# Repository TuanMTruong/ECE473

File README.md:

#Wireless room LED controller
ECE 473 project.

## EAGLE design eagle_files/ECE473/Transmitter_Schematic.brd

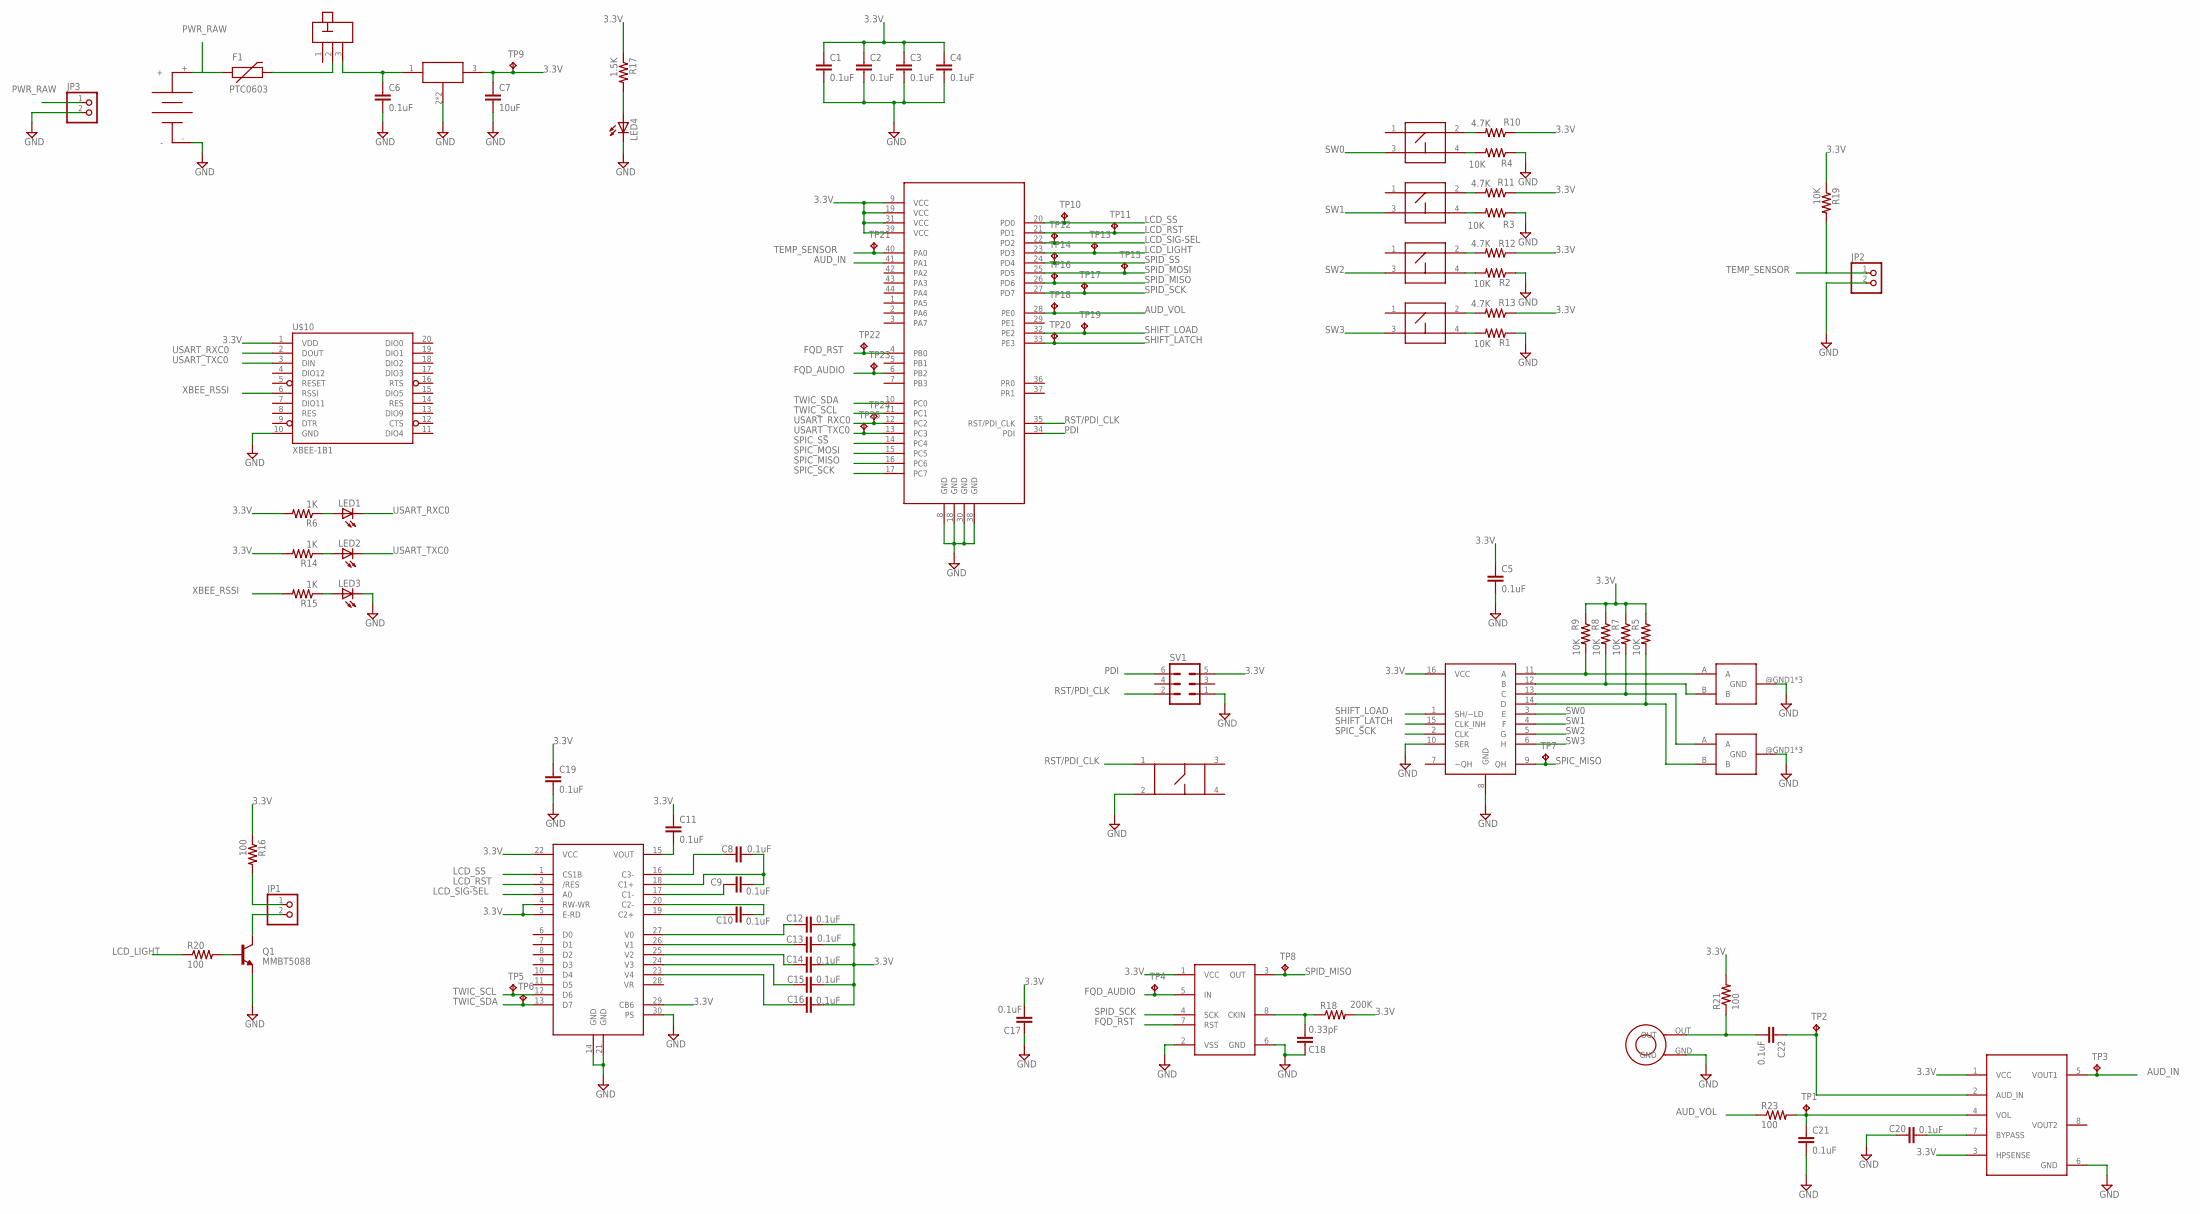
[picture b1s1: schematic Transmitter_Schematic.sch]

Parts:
C1, C2, C3, C4, C5, C6, C8, C9, C10, C11, C12, C13, C14, C15, C16, C17, C19, C20, C21, C22: 0.1uF; 0603-CAP
C7: 10uF; 0603-CAP
C18: 0.33pF; 0603-CAP
F1: PTC0603; 0603
JP1, JP2, JP3: PINHD-1X2; 1X02
LED1, LED2, LED3, LED4: LED0603; LED-0603
Q1: MMBT5088; SOT23
R1, R2, R3, R4, R5, R7, R8, R9, R19: 10K; 0603-RES
R6, R14, R15: 1K; 0603-RES
R10, R11, R12, R13: 4.7K; 0603-RES
R16, R20, R21, R23: 100; 0603-RES
R17: 1.5K; 0603-RES
R18: 200K; 0603-RES
SV1: MA03-2
SW0, SW1, SW2, SW3: SPARKFUN_TAC_BUTTONS
TP1, TP2, TP3, TP4, TP5, TP6, TP7, TP8, TP9, TP10, TP11, TP12, TP13, TP14, TP15, TP16, TP17, TP18, TP19, TP20, TP21, TP22, TP23, TP24, TP25: TPPAD1-13; P1-13
U$1: ATXMEGA32A4UTQFP44; QFP80P1200X1200X120-44N
U$6: 8B_SHIFT_REG; TSSOP16
U$7: MICRO_TAC_BUTTONS
U$8, U$9: ENCODER; EVE_GE1F2012B
U$10: XBEE-1B1; XBEE-1
U$11: LCD_CONNECTOR
U$12: 3.3V_REG_LDO; SOT223
U$13: 3XAA_BATT_HOLDER
U$14: SWITCH_SLIDE
U$15: FREQUENCY_DIVIDER; DIP08
U$16: LM4875; SOIC8
U$17: MICROPHONE; CMA-4544PF

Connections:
3.3V: C1.1, C2.1, C3.1, C4.1, C5.1, C7.1, C11.1, C12.2, C13.2, C14.2, C15.2, C16.2, C17.2, C19.1, R5.1, R6.2, R7.1, R8.1, R9.1, R10.1, R11.1, R12.1, R13.1, R14.2, R16.1, R17.1, R18.2, R19.1, R21.2, SV1.5, TP9.TP, U$1.9 (VCC), U$1.19 (VCC), U$1.31 (VCC), U$1.39 (VCC), U$6.16 (VCC), U$10.1 (VDD), U$11.4 (RW-WR), U$11.5 (E-RD), U$11.22 (VCC), U$11.29 (CB6), U$12.3, U$15.1 (VCC), U$16.1 (VCC), U$16.3 (HPSENSE)
AUD_IN: TP3.TP, U$1.41 (PA1), U$16.5 (VOUT1)
AUD_VOL: R23.1, TP18.TP, U$1.28 (PE0)
FQD_AUDIO: TP4.TP, TP23.TP, U$1.6 (PB2), U$15.5 (IN)
FQD_RST: TP22.TP, U$1.4 (PB0), U$15.7 (RST)
GND: C1.2, C2.2, C3.2, C4.2, C5.2, C6.2, C7.2, C17.1, C18.1, C19.2, C20.1, C21.2, JP2.2, JP3.2, LED3.C, LED4.C, Q1.2 (E), R1.1, R2.1, R3.1, R4.1, SV1.1, U$1.8 (GND), U$1.18 (GND), U$1.30 (GND), U$1.38 (GND), U$6.8 (GND), U$6.10 (SER), U$7.2, U$8.@GND1 (GND), U$8.@GND2 (GND), U$8.GND, U$9.@GND1 (GND), U$9.@GND2 (GND), U$9.GND, U$10.10 (GND), U$11.14 (GND), U$11.21 (GND), U$11.30 (PS), U$12.2, U$12.4, U$13.-, U$15.2 (VSS), U$15.6 (GND), U$16.6 (GND), U$17.GND
LCD_LIGHT: R20.1, TP13.TP, U$1.23 (PD3)
LCD_RST: TP11.TP, U$1.21 (PD1), U$11.2 (/RES)
LCD_SIG-SEL: TP12.TP, U$1.22 (PD2), U$11.3 (A0)
LCD_SS: TP10.TP, U$1.20 (PD0), U$11.1 (CS1B)
MIC_IN: C22.1, TP2.TP, U$16.2 (AUD_IN)
unnamed: R2.2, SW2.4
unnamed: C6.1, U$12.1, U$14.3
unnamed: C8.1, U$11.16 (C3-)
unnamed: C8.2, C9.2, U$11.18 (C1+)
unnamed: R3.2, SW1.4
unnamed: R4.2, SW0.4
unnamed: R1.2, SW3.4
unnamed: R5.2, U$6.14 (D), U$9.B
unnamed: C9.1, U$11.17 (C1-)
unnamed: R9.2, U$6.11 (A), U$8.A
unnamed: R8.2, U$6.12 (B), U$8.B
unnamed: R7.2, U$6.13 (C), U$9.A
unnamed: C10.2, U$11.20 (C2-)
unnamed: R10.2, SW0.2
unnamed: R11.2, SW1.2
unnamed: R12.2, SW2.2
unnamed: R13.2, SW3.2
unnamed: C10.1, U$11.19 (C2+)
unnamed: C12.1, U$11.27 (V0)
unnamed: C13.1, U$11.26 (V1)
unnamed: C14.1, U$11.25 (V2)
unnamed: C15.1, U$11.24 (V3)
unnamed: C16.1, U$11.23 (V4)
unnamed: JP1.1, R16.2
unnamed: C11.2, U$11.15 (VOUT)
unnamed: JP1.2, Q1.3 (C)
unnamed: F1.2, U$14.2
unnamed: LED1.A, R6.1
unnamed: LED2.A, R14.1
unnamed: LED3.A, R15.1
unnamed: LED4.A, R17.2
unnamed: Q1.1 (B), R20.2
unnamed: C22.2, R21.1, U$17.OUT
unnamed: C21.1, R23.2, TP1.TP, U$16.4 (VOL)
unnamed: C20.2, U$16.7 (BYPASS)
unnamed: C18.2, R18.1, U$15.8 (CKIN)
PDI: SV1.6, U$1.34 (PDI)
PWR_RAW: F1.1, JP3.1, U$13.+
RST/PDI_CLK: SV1.2, U$1.35 (RST/PDI_CLK), U$7.1
SHIFT_LATCH: TP20.TP, U$1.33 (PE3), U$6.15 (CLK_INH)
SHIFT_LOAD: TP19.TP, U$1.32 (PE2), U$6.1 (SH/~LD)
SPIC_MISO: TP7.TP, U$1.16 (PC6), U$6.9 (QH)
SPIC_MOSI: U$1.15 (PC5)
SPIC_SCK: U$1.17 (PC7), U$6.2 (CLK)
SPIC_SS: U$1.14 (PC4)
SPID_MISO: TP8.TP, TP16.TP, U$1.26 (PD6), U$15.3 (OUT)
SPID_MOSI: TP15.TP, U$1.25 (PD5)
SPID_SCK: TP17.TP, U$1.27 (PD7), U$15.4 (SCK)
SPID_SS: TP14.TP, U$1.24 (PD4)
SW0: SW0.3, U$6.3 (E)
SW1: SW1.3, U$6.4 (F)
SW2: SW2.3, U$6.5 (G)
SW3: SW3.3, U$6.6 (H)
TEMP_SENSOR: JP2.1, R19.2, TP21.TP, U$1.40 (PA0)
TWIC_SCL: TP5.TP, U$1.11 (PC1), U$11.12 (D6)
TWIC_SDA: TP6.TP, U$1.10 (PC0), U$11.13 (D7)
USART_RXC0: LED1.C, TP24.TP, U$1.12 (PC2), U$10.2 (DOUT)
USART_TXC0: LED2.C, TP25.TP, U$1.13 (PC3), U$10.3 (DIN)
XBEE_RSSI: R15.2, U$10.6 (RSSI)

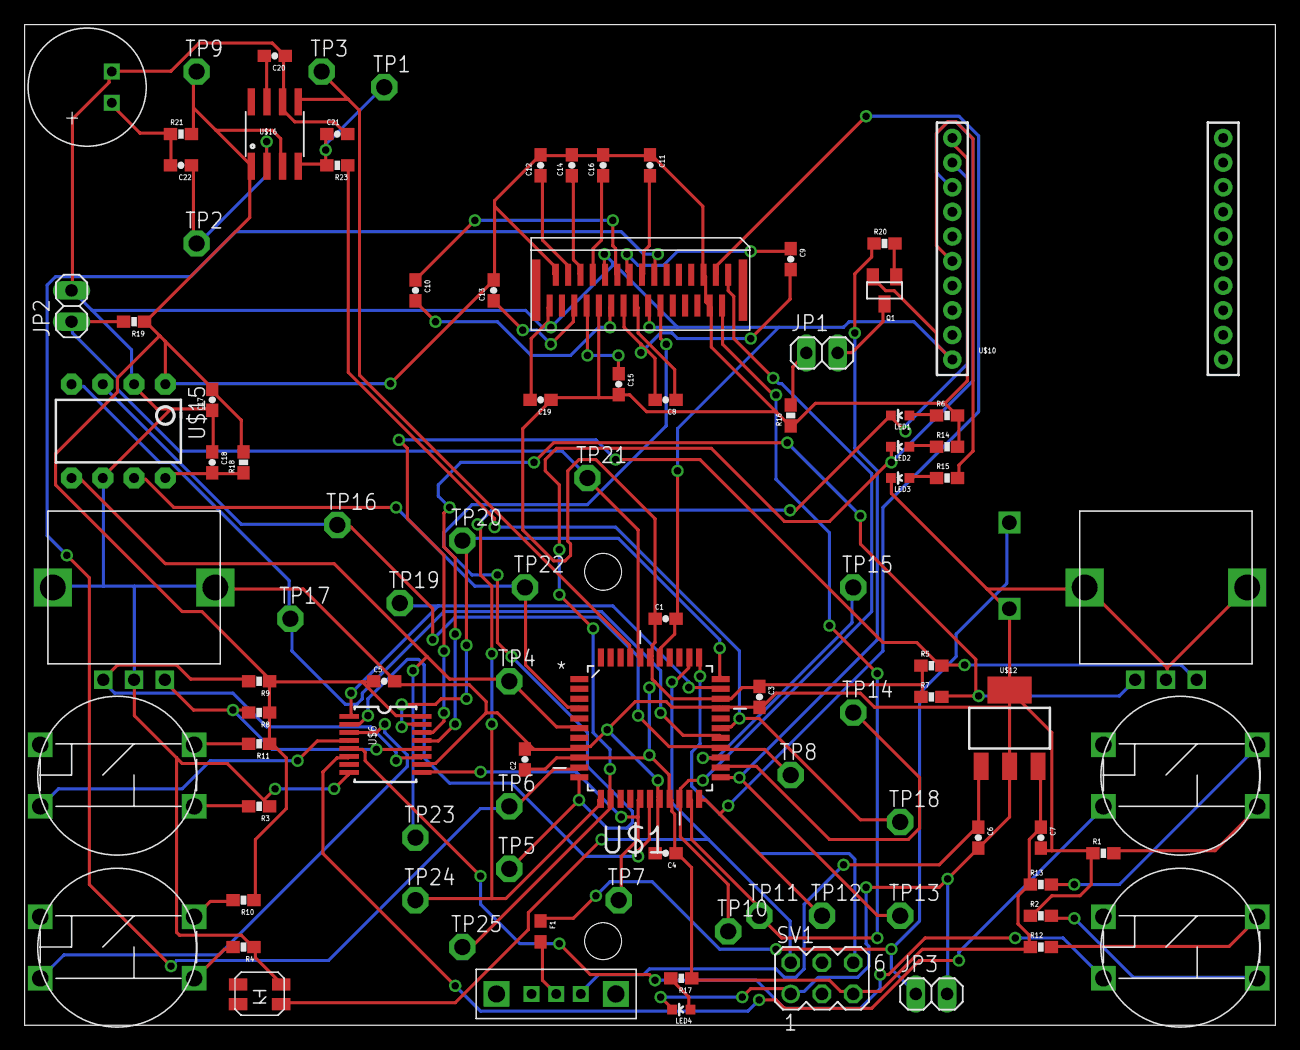
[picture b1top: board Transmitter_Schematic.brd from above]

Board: 2 copper layers, 101.6 x 81.3 mm, 96 parts (1 on the bottom side), 68 nets.

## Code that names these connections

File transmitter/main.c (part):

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// - Push buttons & Encoder on SPIC
//	- SPIC_SS 	PC4
//	- SPIC_MOSI 	PC5
//	- SPIC_MISO	PC6
//	- SPIC_SCK	PC7
//	- SHIFT_LOAD	PE2
//	- SHIFT_LATCH	PE3
// - Frequency divider on SPID
//	- SPID_SS	PD4
//	- SPID_MOSI	PD5
//	- SPID_MISO	PD6
//	- SPID_SCK	PD7
//	- FQD_RST	PB0
//	- FQD_AUDIO	PB2
// - LCD on TWIC
//	- TWIC_SDA	PC0
//	- TWIC_SCL	PC1
//	- LCD_SS	PD0
//	- LCD_RST	PD1
//	- LCD_SIG	PD2
//	- LCD_LIGHT	PD3
// - XBEE on USARTC0
//	- USART_RXCO	PC2
//	- USART_TXC0	PC3
// - Audio in
// 	- AUD_IN 	PA1
//	- AUD_VOL	PE0
// - Temp Sensor
//	- TEMP		PA0
//
//
//
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/******************************************************************/
//macros
/******************************************************************/
#define AUD_IN_PIN	PIN1_bm
#define AUD_VOL_PIN	PIN0_bm
#define TEMP_PIN	PIN0_bm

#define OPEN_COM    0xFF    //starting communication byte from USART
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/******************************************************************/
void Setup_DDR(void){
	//1 = output, 0 = input
	PORTE.DIRSET = SHIFT_LATCH_PIN | SHIFT_LOAD_PIN | AUD_VOL_PIN;
	PORTB.DIRSET = FQD_RST_PIN | FQD_AUDIO_PIN;
	PORTD.DIRSET = LCD_SS_PIN | LCD_RST_PIN | LCD_SIG_PIN | LCD_LIGHT_PIN;

	//set audio and temp sensor to input
	PORTA.DIRCLR = AUD_IN_PIN | TEMP_PIN;
	return;
}

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	//}


	PORTD.OUTSET = LCD_LIGHT_PIN;   //lCD back light on
	LCD_update();                   //write to LCD (WIP)
    
	while(1){
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
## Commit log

2013-10-21 I will add my files later... need to work on senior design
2013-10-21 Added the transmitter and reciever block diagram
2013-11-10 added starting source code for receiver
2013-11-10 updated receiver code
2013-11-10 added data buffer
2013-11-10 added base code to transmitter main.c
2013-11-20 moved rc file
2013-11-25 add board files
2013-12-01 WIP: xbee setup
2013-12-02 WIP: testing spi read input
2013-12-03 WIP: rgb to hs converter
2013-12-03 WIP: Finished wireless protocol
2013-12-03 WIP: wireless protocol
2013-12-03 WIP: Trying to fix the flickering light thing -_-
2013-12-04 WIP: cleaning up code:
2013-12-05 Ready for show and tell =) (but still needs work)
2013-12-05 WIP: 99 bugs on the wall, 99 bugs on the wall, take one down, passing it around, 127 bugs on the wall...
2013-12-14 The buttons are more responsive and the encoder bug is fixed
2013-12-16 Debugged twi for rtc communication
2013-12-16 WIP: lcd functions
2013-12-16 cleaning
2013-12-16 more comments
2013-12-16 WIP: LCD
2015-03-05 Finally adding some documentation (still meh)

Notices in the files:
parts and their libraries:
SparkFun-Capacitors: Licensing: CC v3.0 Share-Alike You are welcome to use this library for commercial purposes.
